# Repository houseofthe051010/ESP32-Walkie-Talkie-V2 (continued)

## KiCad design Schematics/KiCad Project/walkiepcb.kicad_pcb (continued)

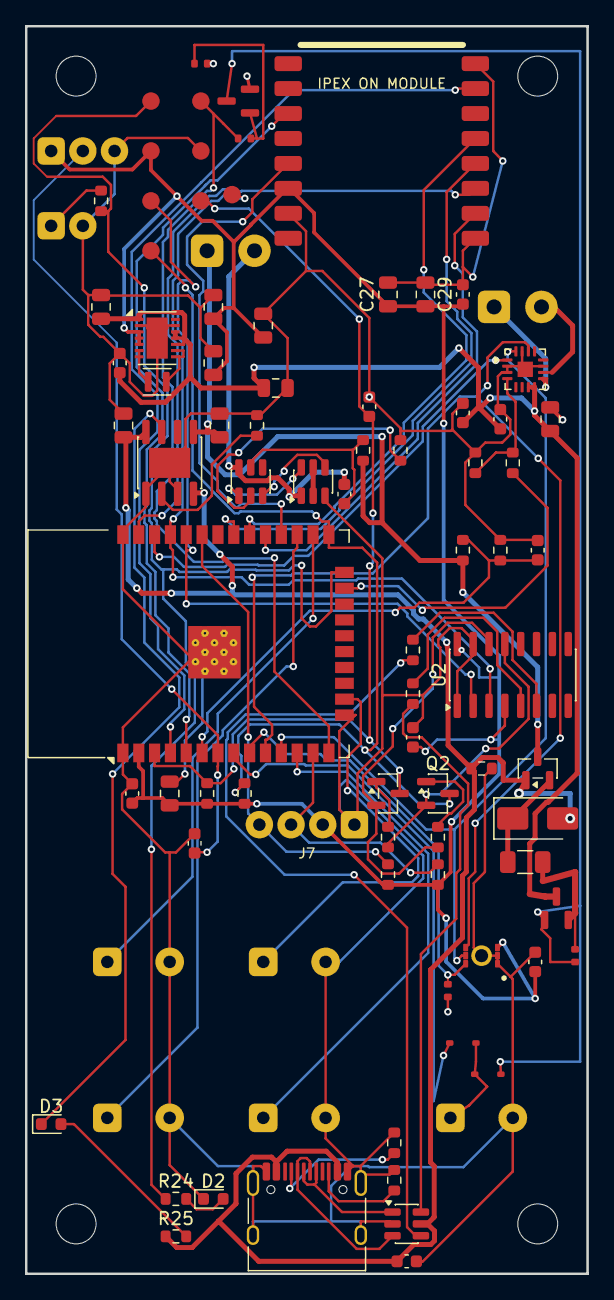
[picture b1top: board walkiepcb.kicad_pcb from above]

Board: 2 copper layers, 45.0 x 100.0 mm, 93 parts (0 on the bottom side), 65 nets.

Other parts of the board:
H1, H2, H3, H4: MountingHole_3.2mm_M3

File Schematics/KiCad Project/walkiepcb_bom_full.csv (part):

"Reference","Value","Footprint","Manufacturer","MPN","JLC/LCSC","JLC Classification","Economic Compatible","DNP","Notes","QUANTITY"
"C1,C7,C9,C12,C14-C16,C26,C29,C30","100n","Capacitor_SMD:C_0603_1608Metric","YAGEO","CC0603KRX7R9BB104","C14663","Basic","YES","NO","ADC acquisition reservoir; 5ms Thevenin RC,Buck-boost VINA bypass; place at VINA/GND,Connector-local VBUS bypass,DW01 supply filter,ESP32 local HF bypass,ICS-43432 local bypass; place directly between VDD and GND,MAX98357A local bypass,Potentiometer ADC filter,Ra-01SH/CH340C local high-frequency decoupling","10"
"C4,C17","1u","Capacitor_SMD:C_0603_1608Metric","Samsung Electro-Mechanics","CL10A105KB8NNNC","C15849","Basic","YES","NO","ESP32 EN power-on delay,MAX98357A local mid-band bypass","2"
"C5,C6,C8,C13,C18,C20","10u","Capacitor_SMD:C_0805_2012Metric","Samsung Electro-Mechanics","CL21A106KAYNNNE","C15850","Basic","YES","NO","Buck-boost input capacitor 2; TPS63021 reference design uses 2x10uF at VIN/PGND,Buck-boost input capacitor; place at VIN/PGND,ESP32 local bulk,MAX98357A local bulk,TP4056 battery bypass,TP4056 input bulk","6"
"C10,C11,C19,C27,C28","22u","Capacitor_SMD:C_0805_2012Metric","Samsung Electro-Mechanics","CL21A226MAQNNNE","C45783","Basic","YES","NO","Ra-01SH local bulk decoupling,TPS63021 output capacitor 1; place at VOUT/PGND,TPS63021 output capacitor 2; place at VOUT/PGND,TPS63021 output capacitor 3; 66uF nominal bank follows TI stability matrix","5"
"D1","SS34","Diode_SMD:D_SMA","MDD","SS34","C8678","Basic","YES","NO","USB-to-system Schottky; anode USB, cathode SYS_RAW","1"
"D2,D3","KT-0603R","LED_SMD:LED_0603_1608Metric","Hubei KENTO","KT-0603R","C2286","Basic","YES","NO","On-board status LED,TP4056 charging indicator; on while charging","2"
"D5,D6","1N4148WS","Diode_SMD:D_SOD-323","Jiangsu Changjing Electronics Technology","1N4148WS","C2128","Basic","YES","NO","BTN5 sense diode; A=BTN5 K=BTN5_SW,BTN5 start diode; A=PWR_GATE K=BTN5_SW","2"
"F1","1206L200PR 2A hold / 3.5A trip","Fuse:Fuse_1206_3216Metric","Littelfuse","1206L200PR","C151163","Extended","YES","NO","Resettable system fault protection","1"
"J1","USB-C / charge + program","Connector_USB:USB_C_Receptacle_HRO_TYPE-C-31-M-12","Korean Hroparts Elec","TYPE-C-31-M-12","C165948","Extended","YES","NO","USB 2.0 sink; shell grounded","1"
"J2","BAT+ / BAT-","walkiepcb:WirePads_2_P5.08mm","Hand-wired","2 solder pads","","DNP","YES","YES","Battery wires; BAT- is cell negative before protection FETs","1"
"J4","SPK+ / SPK-","walkiepcb:WirePads_2_P5.08mm","Hand-wired","2 solder pads","","DNP","YES","YES","Differential Class-D output; neither terminal is ground","1"
"J5","3V3 / POT_ADC / GND","walkiepcb:WirePads_3_P2.54mm","Hand-wired","3 solder pads","","DNP","YES","YES","External potentiometer; exactly three holes","1"
"J6","LED+ / LED-","walkiepcb:WirePads_2_P2.54mm","Hand-wired","2 solder pads","","DNP","YES","YES","External LED; exactly two holes","1"
"J7","OLED MODULE: GND / 3V3 / SCL / SDA","walkiepcb:OLED_1x04_P2.54mm_HolesOnly","Hand-wired","2.54mm 1x4 header","","DNP","YES","YES","For a commercial SSD1306 I2C module; verify the module pin order before wiring","1"
"L1","2.2uH / 4.2A Isat","Inductor_SMD:L_Murata_DFE201610P","Sunlord","MWTC201610S2R2MT","C6807735","Extended","YES","NO","123mohm; 2.3A Irms; 4.2A Isat; buck-boost energy-transfer inductor","1"
"MK1","ICS-43432 (bottom-port I2S)","walkiepcb:ICS-43432_LGA7_4x3mm","TDK InvenSense","ICS-43432","C574021","Extended","YES","NO","Economic-compatible but high-difficulty assembly; stocked bottom-port I2S microphone","1"
"Q1,Q2,Q6","MMBT3904","Package_TO_SOT_SMD:SOT-23","CJ (Changjiang Electronics Tech)","MMBT3904","C20526","Basic","YES","NO","CH340C DTR/RTS automatic-programming transistor,Firmware-controlled main-gate pull-down","3"
"Q3","FS8205A dual NMOS","Package_TO_SOT_SMD:SOT-23-6","FUXINSEMI","FS8205A","C908265","Extended","YES","NO","Back-to-back common-drain battery-protection MOSFET; verified FUXINSEMI pinout","1"
"Q4,Q5","AO3401A","Package_TO_SOT_SMD:SOT-23","Alpha & Omega Semiconductor","AO3401A","C15127","Basic","YES","NO","Main soft-power high-side P-MOSFET; S=SYS_FUSED D=SYS_SW,P-channel ideal battery path; S=SYS_RAW D=BAT_CELL","2"
"R1,R2","5.1k","Resistor_SMD:R_0603_1608Metric","UNI-ROYAL","0603WAF5101T5E","C23186","Basic","YES","NO","USB-C Rd","2"
"R3,R4","22","Resistor_SMD:R_0603_1608Metric","UNI-ROYAL","0603WAF220JT5E","C23345","Basic","YES","NO","USB D+ series termination; place near CH340C,USB D- series termination; place near CH340C","2"
"R5,R6,R22,R23","10k","Resistor_SMD:R_0603_1608Metric","UNI-ROYAL","0603WAF1002T5E","C25804","Basic","YES","NO","CH340C automatic-programming transistor base resistor,ESP32 EN pull-up,ESP32 boot pull-up","4"
"R7,R20","2.4k","Resistor_SMD:R_0603_1608Metric","UNI-ROYAL","0603WAF2401T5E","C22940","Basic","YES","NO","Limits SD_MODE clamp current if raw VDD falls below 3V3,Sets TP4056 current ≈500mA","2"
"R8","100","Resistor_SMD:R_0603_1608Metric","UNI-ROYAL","0603WAF1000T5E","C22775","Basic","YES","NO","DW01 supply filter","1"
"R9","1k","Resistor_SMD:R_0603_1608Metric","UNI-ROYAL","0603WAF1001T5E","C21190","Basic","YES","NO","DW01 current-sense input filter","1"
"R10,R13,R14,R19","100k","Resistor_SMD:R_0603_1608Metric","UNI-ROYAL","0603WAF1003T5E","C25803","Basic","YES","NO","Battery divider lower,Battery divider upper,Keeps amplifier shut down during boot,PMOS gate pull-down","4"
"R15,R16","4.7k","Resistor_SMD:R_0603_1608Metric","UNI-ROYAL","0603WAF4701T5E","C23162","Basic","YES","NO","I2C pull-up","2"
"R21,R24,R25","330","Resistor_SMD:R_0603_1608Metric","UNI-ROYAL","0603WAF3300T5E","C23138","Basic","YES","NO","Indicator current limit; reuses existing Basic BOM line,≈3.9mA for 2.0V LED at 3.3V","3"
"R26-R28,R30","100k","Resistor_SMD:R_0402_1005Metric","UNI-ROYAL","0402WGF1003TCE","C25741","Basic","YES","NO","GPIO12 hold base-current limit,ICS-43432 SD pulldown required while microphone output is tri-stated,Latch-transistor base pull-down,Main P-MOS gate pull-up","4"
"SW1","BTN1 / hand-solder","walkiepcb:SW_Tactile_2Pin_6x6mm_P5.0mm","E-Switch or equivalent","TL1100F100QG","","DNP","YES","YES","Exactly two plated holes; ESP32 internal pull-up","1"
"SW2","BTN2 / hand-solder","walkiepcb:SW_Tactile_2Pin_6x6mm_P5.0mm","E-Switch or equivalent","TL1100F100QG","","DNP","YES","YES","Exactly two plated holes; ESP32 internal pull-up","1"
"SW3","BTN3 / hand-solder","walkiepcb:SW_Tactile_2Pin_6x6mm_P5.0mm","E-Switch or equivalent","TL1100F100QG","","DNP","YES","YES","Exactly two plated holes; ESP32 internal pull-up","1"
"SW4","BTN4 / hand-solder","walkiepcb:SW_Tactile_2Pin_6x6mm_P5.0mm","E-Switch or equivalent","TL1100F100QG","","DNP","YES","YES","Exactly two plated holes; ESP32 internal pull-up","1"
"SW5","BTN5 POWER / FUNCTION","walkiepcb:SW_Tactile_2Pin_6x6mm_P5.0mm","E-Switch or equivalent","TL1100F100QG","","DNP","YES","YES","Hold 2 s for firmware-validated power on/off; pulls PWR_GATE low","1"
"TP1","3V3","walkiepcb:TestPad_1.0mm","PCB pad","SMD test pad","","PCB","YES","YES","Probe-only test pad","1"
"TP2","GND","walkiepcb:TestPad_1.0mm","PCB pad","SMD test pad","","PCB","YES","YES","Probe-only test pad","1"
"TP3","TX0","walkiepcb:TestPad_1.0mm","PCB pad","SMD test pad","","PCB","YES","YES","Probe-only test pad","1"
"TP4","RX0","walkiepcb:TestPad_1.0mm","PCB pad","SMD test pad","","PCB","YES","YES","Probe-only test pad","1"
"TP5","EN","walkiepcb:TestPad_1.0mm","PCB pad","SMD test pad","","PCB","YES","YES","Probe-only test pad","1"
"TP6","GPIO0","walkiepcb:TestPad_1.0mm","PCB pad","SMD test pad","","PCB","YES","YES","Probe-only test pad","1"
"TP7","LED_STATUS","walkiepcb:TestPad_1.0mm","PCB pad","SMD test pad","","PCB","YES","YES","Optional expansion solder/test pad","1"
"TP8","PWR_HOLD / GPIO12","walkiepcb:TestPad_1.0mm","PCB pad","SMD test pad","","PCB","YES","YES","Soft-power hold output and diagnostic pad; GPIO12 boot strap","1"
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
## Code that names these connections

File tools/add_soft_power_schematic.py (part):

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
Operation:
* pressing BTN5 directly pulls the main P-MOS gate low and wakes the board;
* firmware only asserts GPIO12/PWR_HOLD after BTN5 has remained held for 2 s;
* while running, firmware releases PWR_HOLD after a 2 s BTN5 shutdown hold;
* D5 pulls the PMOS gate down from the button node, while D6 lets GPIO32
  sense that node without exposing an unpowered ESP32 to the cell.
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    # Remove the obsolete two-hole external power-switch symbol and labels.
    start, end, _ = symbol_block(text, "J3")
    text = text[:start] + text[end:]
    text = remove_label_at(text, "SYS_FUSED", "312.42", "111.76")
    text = remove_label_at(text, "SYS_SW", "312.42", "114.3")

    # BTN5 grounds a separate switch node. D5 uses that node to start the PMOS;
    # D6 reports the physical button state to GPIO32 independently of Q6.
    text = replace_label_at(text, "BTN5", "339.09", "306.07", "BTN5_SW")
    start, end, sw5 = symbol_block(text, "SW5")
    sw5 = set_property(sw5, "Value", "BTN5 POWER / FUNCTION")
    sw5 = set_property(sw5, "Notes", "Hold 2 s for firmware-validated power on/off; pulls PWR_GATE low")
    text = text[:start] + sw5 + text[end:]

    # GPIO12 becomes the hold output. TP8 remains a useful diagnostic pad.
    text = replace_label_at(text, "GPIO12", "81.28", "207.01", "PWR_HOLD")
    text = replace_label_at(text, "GPIO12", "276.86", "331.47", "PWR_HOLD")
    start, end, tp8 = symbol_block(text, "TP8")
    tp8 = set_property(tp8, "Value", "PWR_HOLD / GPIO12")
    tp8 = set_property(tp8, "Notes", "Soft-power hold output and diagnostic pad; GPIO12 boot strap")
    text = text[:start] + tp8 + text[end:]

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        clone_symbol(text, "D1", "D5", 345.44, 157.48, 0, diode | {"Notes": "BTN5 start diode; A=PWR_GATE K=BTN5_SW"}),
        clone_symbol(text, "D1", "D6", 365.76, 157.48, 0, diode | {"Notes": "BTN5 sense diode; A=BTN5 K=BTN5_SW"}),
        # Q5: G, S, D.
        label("PWR_GATE", 297.18, 137.16, 180),
        label("SYS_FUSED", 304.80, 132.08, 90),
        label("SYS_SW", 304.80, 142.24, 270),
        # Q6: B, E, C.
        label("PWR_LATCH_BASE", 317.50, 137.16, 180),
        label("GND", 325.12, 132.08, 90),
        label("PWR_GATE", 325.12, 142.24, 270),
        # Vertical resistor pins at y +/- 3.81 mm.
        label("SYS_FUSED", 297.18, 153.67, 90),
        label("PWR_GATE", 297.18, 161.29, 270),
        label("PWR_LATCH_BASE", 312.42, 153.67, 90),
        label("GND", 312.42, 161.29, 270),
        label("PWR_HOLD", 327.66, 153.67, 90),
        label("PWR_LATCH_BASE", 327.66, 161.29, 270),
        # D_Schottky-compatible graphic: pin 1/K left, pin 2/A right.
        label("BTN5_SW", 341.63, 157.48, 180),
        label("PWR_GATE", 349.25, 157.48, 0),
        label("BTN5_SW", 361.95, 157.48, 180),
        label("BTN5", 369.57, 157.48, 0),
        note(
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            294.64,
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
